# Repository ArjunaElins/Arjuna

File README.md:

ARJUNA
======

Arjuna is an ODROID based piano learning device. It is created to help the visually impaired to learn to play piano. With Arjuna, we hope to open them a new window to the beautiful world of music.

## Hardware

Arjuna has two main parts, the MPU (MIDI Processing Unit) and the Hands Module.
Here’s the components for both parts:

#### MIDI Processing Unit

1. [ODROID-C1](http://www.hardkernel.com/main/products/prdt_info.php?g_code=G141578608433)
2. nRF24L01+ Transceiver Module
3. Keypad

#### Hands Module

1. [Arduino Pro Micro](https://www.sparkfun.com/products/12640)
2. nRF24L01+ Transceiver Module
3. Small Vibration Motor
4. 1 Cell LiPo Battery
5. 5V Step-up Voltage Regulator
6. 3D Printed Ring
7. 3D Printed Case

## Documentation

* [Components](https://github.com/ArjunaElins/Arjuna/blob/master/Docs/Components.md)
* [Assembly Guide](https://github.com/ArjunaElins/Arjuna/blob/master/Docs/Assembly.md)
* [Installation Guide](https://github.com/ArjunaElins/Arjuna/blob/master/Docs/Installation.md)
* [How It Works](https://github.com/ArjunaElins/Arjuna/blob/master/Docs/HowItWorks.md)
* [About The Project](https://github.com/ArjunaElins/Arjuna/blob/master/Docs/About.md)

## Developer

Arjuna is developed by a three person team from Gadjah Mada University, Indonesia.

* Ilham Imaduddin
* Ahmad Shalahuddin
* Piquitha Della Audyna

## License

This project is licensed under the terms of the [MIT License](http://opensource.org/licenses/MIT).

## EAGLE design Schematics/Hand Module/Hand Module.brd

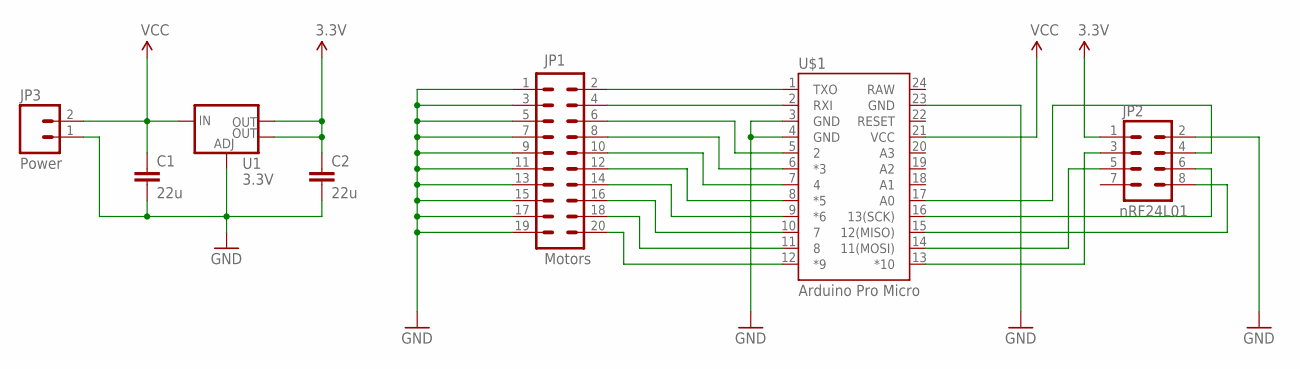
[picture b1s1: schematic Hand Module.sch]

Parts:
C1, C2: 22u; 0805
JP1: Motors; 2X10
JP2: nRF24L01; 2X4
JP3: Power; 1X02
U1: 3.3V; SOT223
U$1: Arduino Pro Micro; ARDUINO_PRO_MICRO

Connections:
1: JP1.2, U$1.1 (TXO)
2: JP1.4, U$1.2 (RXI)
3: JP1.6, U$1.5 (2)
3.3V: C2.1, JP2.1, U1.2 (OUT), U1.4 (OUT)
4: JP1.8, U$1.6 (*3)
5: JP1.10, U$1.7 (4)
6: JP1.12, U$1.8 (*5)
7: JP1.14, U$1.9 (*6)
8: JP1.16, U$1.10 (7)
9: JP1.18, U$1.11 (8)
10: JP1.20, U$1.12 (*9)
GND: C1.2, C2.2, JP1.1, JP1.3, JP1.5, JP1.7, JP1.9, JP1.11, JP1.13, JP1.15, JP1.17, JP1.19, JP2.2, JP3.1, U1.1 (ADJ), U$1.3 (GND), U$1.4 (GND), U$1.23 (GND)
MISO: JP2.8, U$1.15 (12(MISO))
MOSI: JP2.5, U$1.14 (11(MOSI))
unnamed: JP2.3, U$1.13 (*10)
unnamed: JP2.4, U$1.17 (A0)
SCK: JP2.6, U$1.16 (13(SCK))
VCC: C1.1, JP3.2, U1.3 (IN), U$1.21 (VCC)

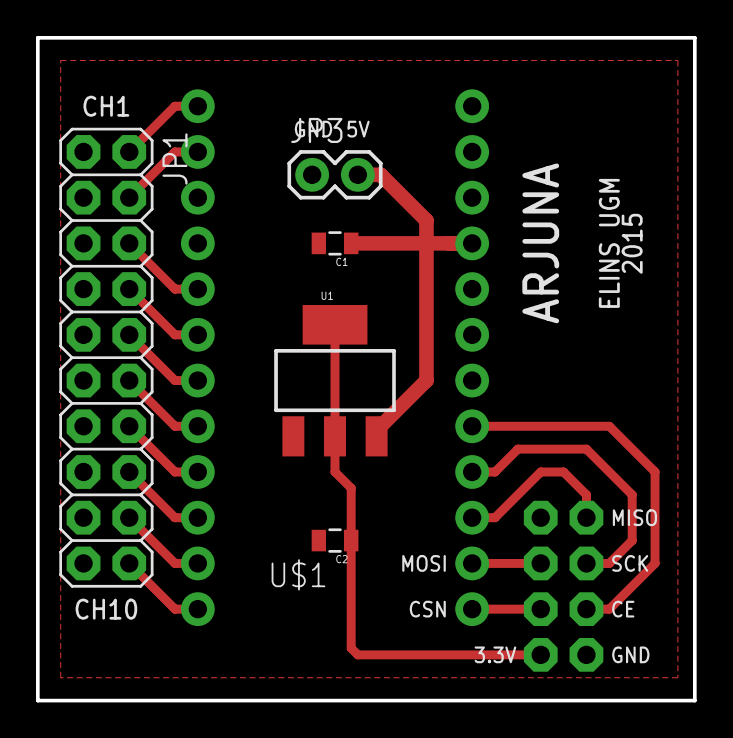
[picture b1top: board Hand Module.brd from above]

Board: 2 copper layers, 36.5 x 36.8 mm, 7 parts (1 on the bottom side), 18 nets.

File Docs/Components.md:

Components
==========

Arjuna has two main parts, the MPU (MIDI Processing Unit) and the Hands Module.
Here’s the components for both parts:

#### MIDI Processing Unit

1. [ODROID-C1](http://www.hardkernel.com/main/products/prdt_info.php?g_code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
2. nRF24L01+ Transceiver Module
3. Keypad

#### Hands Module

1. [Arduino Pro Micro](https://www.sparkfun.com/products/12640)
2. nRF24L01+ Transceiver Module
3. Small Vibration Motor
4. 1 Cell LiPo Battery
5. 5V Step-up Voltage Regulator
6. 3D Printed Ring
7. 3D Printed Case

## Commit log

2015-08-16 Add basic readme file
2015-08-16 Improve Documentation
2015-08-16 Use MIT License
2015-08-16 Add .gitignore
2015-08-17 Add Hand Module Schematic and Board
2015-08-17 Add MPU Readme File
2015-08-17 Add Required Library
2015-08-17 Improve MPU Source Documentation
2015-08-17 Add MPU MidiIO
2015-08-17 Remove Library as Submodule
2015-08-17 Add MPU Source Files
2015-08-17 Add MPU Source Code
2015-08-17 Modify MPU Readme
2015-08-23 Add Motor Support for Hand Module
2015-08-23 Add RF24 Support
2015-08-23 Add Hand Module Documentation
2015-08-24 Fix Hand Module Tranceiver
2015-09-08 Add Hand Selector
2015-09-08 Disable radio debug and fix typos
2015-09-08 Start Refactoring
    With this commit, I start to refactor my code. It is needed to make sure
    the code quality is good. The old code is made in haste, so there's a
    lot of bad code in there.
    This commit add basic main function and command line argument handler.
2015-09-08 Add WiringPi Initialization
    The WiringPi initialization is part of the hardware initialization. It
    is created first because all other hardware initialization is depending
    on it.
2015-09-09 Start Refactoring MidiIO
    This commit creates MidiIO basic initialization header.
2015-09-09 Add MidiIO Initialization Implementation
    This commit implement MidiIO initialization methods and add debuging
    method.
2015-09-09 Open MIDI Input and Output
    This commit add methods to open MIDI input and output port.
2015-09-09 Send and Receive MIDI Message
    This commit add methods to send MIDI message to output port and receive
    MIDI message from input port.
2015-09-09 Remove Debug Level
    Change debug level support to normal enable/disable debug
2015-09-09 Setup MIDI I/O
    This commit add MIDI I/O initialization in main application
2015-09-09 Improve Debug Information
2015-09-09 Setup Radio Transceiver
    Add nRF24L01+ radio transceiver initialization to main application
2015-09-09 Setup Keypad Matrix
    Add keypad matrix initialization in the main application.
2015-09-09 Fix Method Name Case
    Change some method name case to camelCase for consistent naming.
2015-09-09 Add Routine and User Menu
    The routine is an eternal loop to handle user activity.
    The showMenu method shows menu to the user.
    This commit also make changes to .gitignore. Now git will ignore all
    .old data.
2015-09-09 Move Hardware Setup to Separate File
    Originally, setup methods is written in the main file. To simplify the
    main file, all setup and initialization is moved to separate file.
2015-09-09 Implement Container Structure
    This commit implement container structure to hold hardware handler. This
    container will be used to pass hardware handler to other methods.
2015-09-09 Add Song Selector
    The song selector is methods to select song from a list file.
2015-09-09 Fix Compile Errors
    Fix some compile error. The biggest change is to move the getArgs
    function to setup file.
2015-09-09 Fix Setup
    Fix uninitialized container in setup functions.
2015-09-09 Fix Song Selector
    Fix songlist file handler and temporary fix column 3 keypad problem.
2015-09-09 Add MIDI Song Player
    This basic song player can play MIDI file from disk. Vibration feedback
    will be developed next.
2015-09-09 Improve Song Player Design
    This commit separate MIDI player and MIDI data preparation.
2015-09-09 Add Feedback in Song Player
    This commit introduces feedback command in the song player.
2015-09-20 Add Play Mode Selector
    There are three play mode:
    - Both hands
    - Left hand
    - Right hand
    Those three modes can be selected from setPlayMode function.
2015-09-23 Add Play Mode Selector
    This commit introduces getPlayMode function, which is used to ask the
    user for the play mode.
    This commit also move the songPlayer information after the setPlayMode
    is called.
2015-09-23 Remove .gitmodules
    The git modules has been removed from several days ago. I forgot to
    remove the .gitmodules entry
2015-09-23 Delete struct Keyword From Declaration
    Dammit, I forgot it was C++
2015-09-23 Add Button Definition
    Change keypad button from magic value to defined constant
2015-09-23 Add Stopper
    The stopper is a function that called in separate thread to stop the
    player/evaluator in the middle of operation
2015-09-23 Refactor Player
    The player and evaluator is started with identical data preparation. To
    prevent both function use repeated operation, the player is refactored.
    This commit introduces startMPA function, which is a bootstrap for the
    player and evaluator. This function will prepare the data and call
    either player or evaluator depending on user input.
2015-09-23 Add Evaluator Bootstrap
    This commit introduces evaluator function, which is a collection of MIDI
    Evaluation Algorithm.
2015-09-23 Adapt FingerData Class to New MidiFGR Output
    The MidiFGR is changed to produce a simpler file. This commit introduces
    the adaption of FingerData class.
2015-09-23 Dump Unused FingerData Methods
2015-09-23 Dumping MPA
    That last MPA is a real mess. A memory error that I can't understand.
    Maybe it's better to rewrite the algorithm.
2015-09-24 Recreate MIDI Player
    After the last unsolved memory problem, I decided to recreate the MIDI
    Player. It is working good.
2015-09-24 Groups Unison Note
    This commit introduces basic evaluator with a function to group note
    that played at the same time.
2015-09-24 Groups Unison Finger
    Improves evaluator function by adding getUnisonFinger, a function to
    group finger data played at the same time.
2015-09-24 Get MIDI Input
    Improve evaluator function by adding getInput, a function to receive
    MIDI data from input port and group it in a container.
2015-09-24 Evaluate MIDI Input
    This commit introduces a method to compare MIDI data and MIDI Input. It
    works for all three modes. But there's still a bug in left hand mode, it
    force closed in the end of the song.
2015-09-24 Adapt Hand Module to New Schematic
    The hand module schematic is revised, this commit adapt the Arduino Pro
    Micro with the new schematic.
2015-09-25 Reset Buttons
    Change button to original functions.
2015-09-25 Add Feedback On Player
2015-09-25 Add Feedback On Evaluator
2015-09-26 Fixes #5
    The bug fixed by adding direction parameter to the sendFeedback
    function.
2015-09-29 Change Player Vibration to Both Side
    Before, the vibration on player mode is only on one side. After tested,
    it feels better to vibrate on both side.
2015-09-29 Fix #6 MIDI Input Leak
    The leak is closed by making the MIDI IO open only when it's needed.
2015-09-29 Resolve #7 Playback Tempo Modifier
2015-09-29 Remove Evaluator MIDI Output
2015-09-29 Change Hand Selector To Number
    Before, the hand selected by A-C number. We decided to dedicate the A-D
    for menu operation. So the hand selector is moved to 1-3.
2015-09-29 Add Player Stop
    Now user can stop the player by pressing the STOP_BUTTON
2015-09-29 Add Evaluator Stop
    Now user can stop the evaluator by pressing the STOP_BUTTON
2015-09-29 Move MIDI IO Open and Close Function Call
2015-09-29 Resolve #10 Song Playback After Several Mistake
2015-10-03 Fix Keypad Driver
    The new keypad is now working by changing the row. column, and matrix
    values.
    This commit fixes #2 issue.

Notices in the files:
parts and their libraries:
SparkFun-Capacitors: Licensing: Creative Commons ShareAlike 4.0 International - https://creativecommons.org/licenses/by-sa/4.0
